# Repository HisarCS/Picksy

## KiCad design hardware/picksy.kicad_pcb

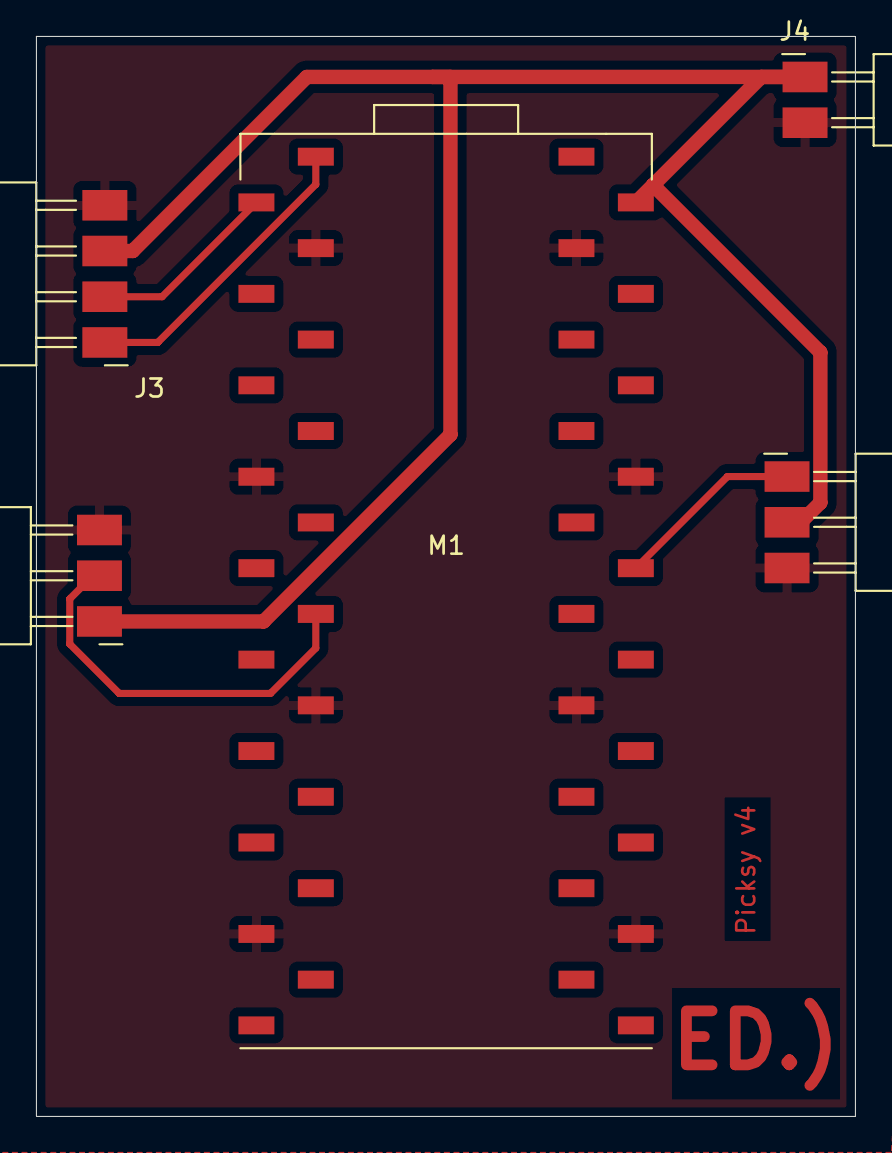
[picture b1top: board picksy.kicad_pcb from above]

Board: 2 copper layers, 45.5 x 60.0 mm, 5 parts (0 on the bottom side), 6 nets.

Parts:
J1: Servo; PinHeader_01x03_P2.54mm_Horizontal_SMD
J2: Mic; PinHeader_01x03_P2.54mm_Horizontal_SMD
J3: OLED; PinHeader_01x04_P2.54mm_Horizontal_SMD
J4: PWR; PinHeader_01x02_P2.54mm_Horizontal_SMD
M1: Module_RaspberryPi_PicoW_Combined; RaspberryPi_PicoW_SocketSMD

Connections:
ANALOG: J2.1, M1.31 (GP26)
GND: J1.3, J2.3, J3.4, J4.2, M1.3 (GND), M1.8 (GND), M1.13 (GND), M1.18 (GND), M1.23 (GND), M1.28 (GND), M1.33 (GND), M1.38 (GND)
GP: J1.2, M1.11 (GP8)
PWR: J1.1, J2.2, J3.3, J4.1, M1.39 (VSYS)
SCL: J3.2, M1.2 (GP1)
SDA: J3.1, M1.1 (GP0)

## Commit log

2025-05-21 main code files aq
2025-05-21 AI done
2025-05-27 BEN OMER DEGILIM,
2025-12-06 Add initial README with project title
2025-12-08 Add newline at end of LevelMenu.js
2025-12-08 Add feedback styles and modify existing classes
